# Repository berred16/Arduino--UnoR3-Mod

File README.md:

# Arduino--UnoR3-Mod
Some modifications of Arduino UNO R3 schematics

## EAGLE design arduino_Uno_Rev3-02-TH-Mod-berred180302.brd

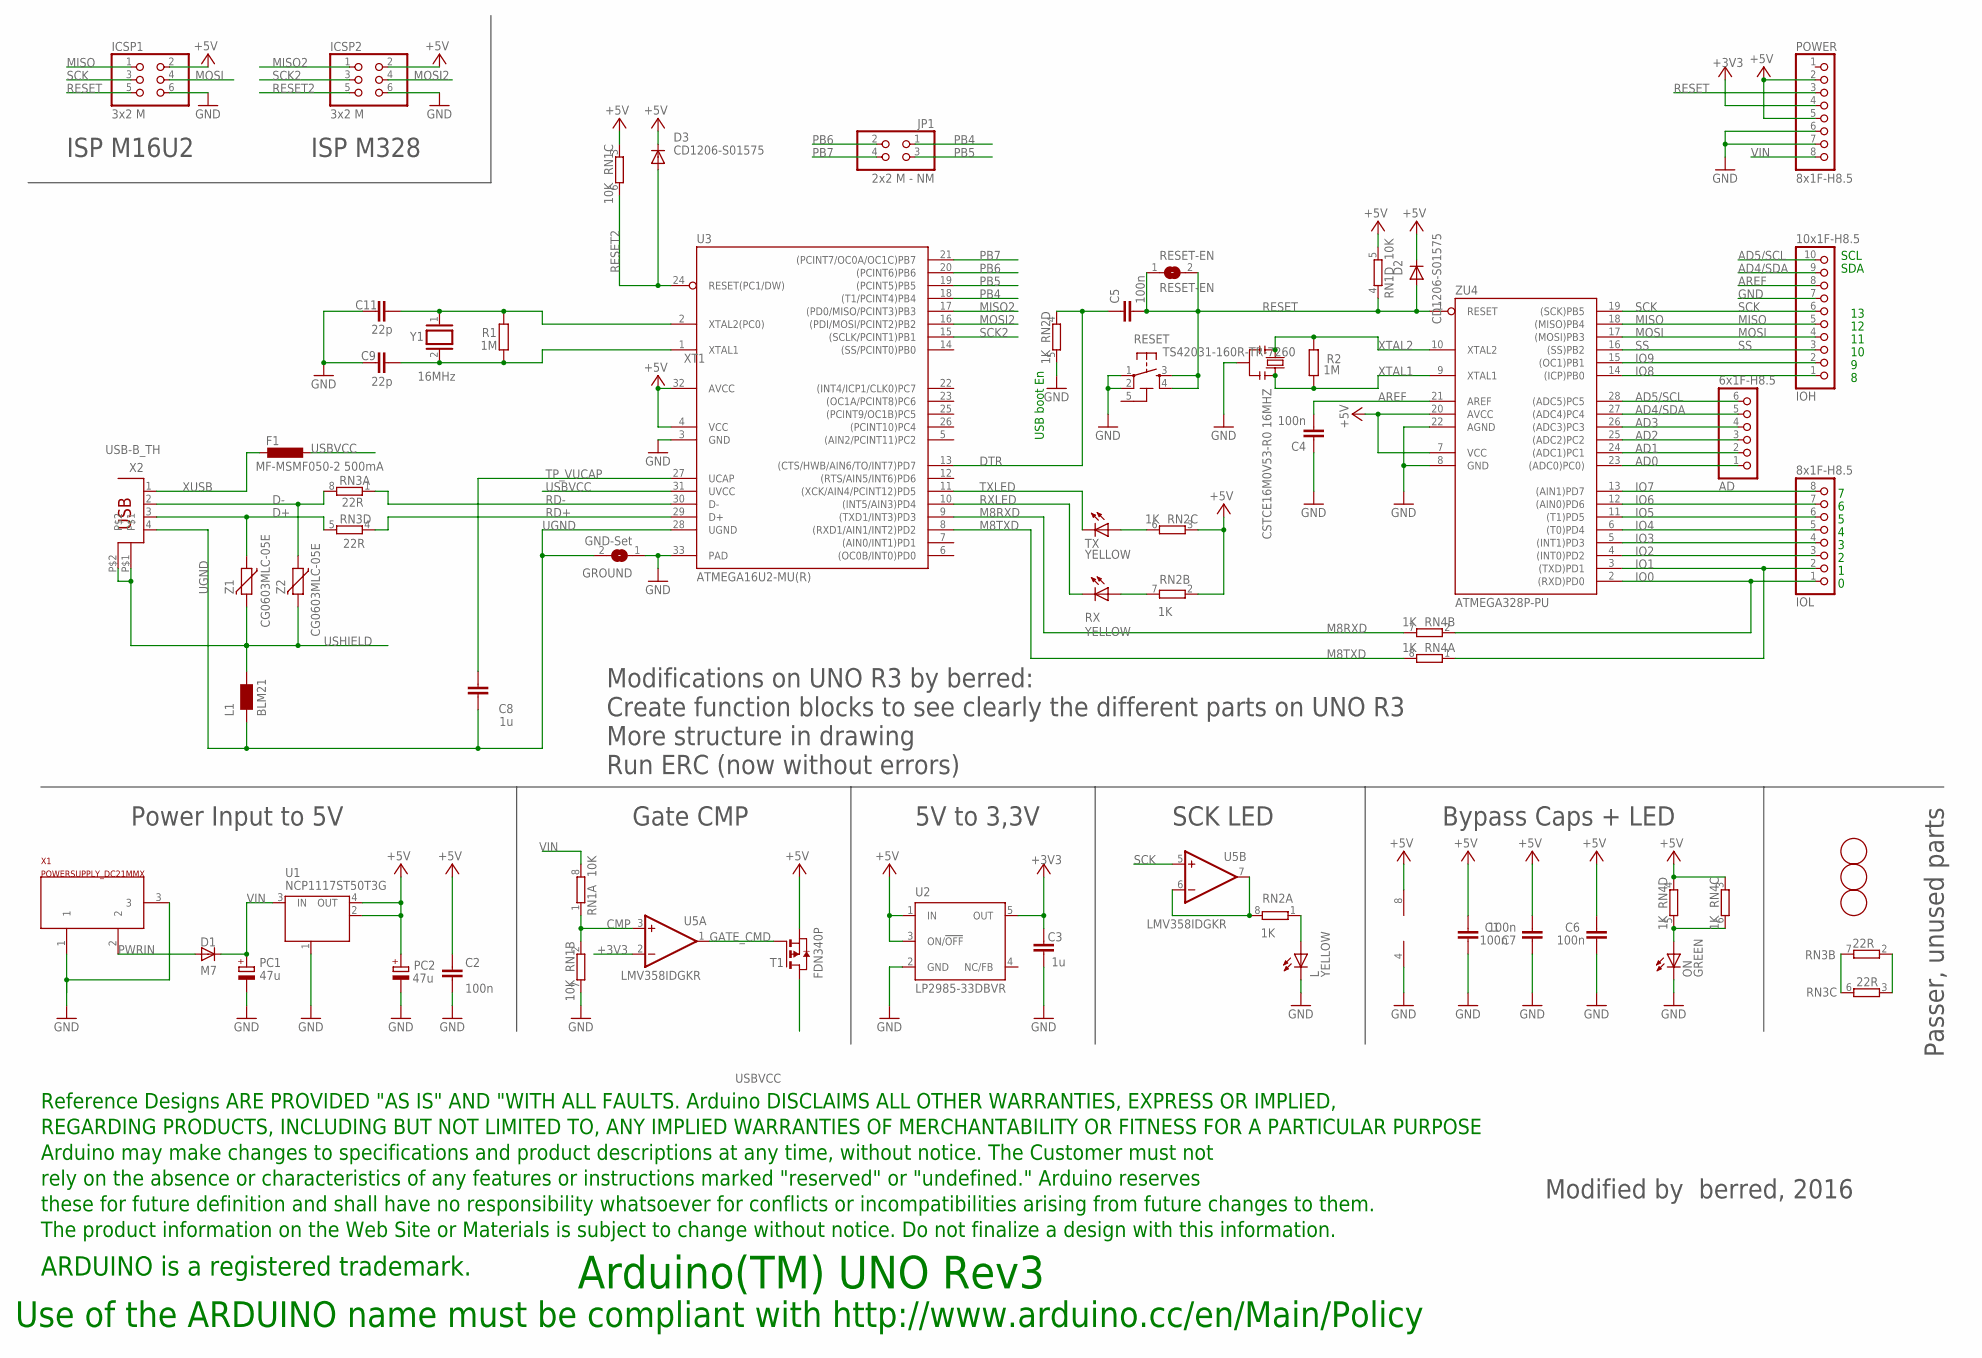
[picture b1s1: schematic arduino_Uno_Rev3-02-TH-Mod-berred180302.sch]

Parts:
AD: 6x1F-H8.5; 1X06
C1, C2, C4, C5, C6, C7: 100n; C0603-ROUND
C3, C8: 1u; C0603-ROUND
C9, C11: 22p; C0603-ROUND
D1: M7; SMB
D2, D3: CD1206-S01575; MINIMELF
F1: MF-MSMF050-2 500mA; L1812
FD1, FD2, FD3: FIDUCIALMOUNT; FIDUCIA-MOUNT
GROUND: GND-Set; SJ
ICSP1, ICSP2: 3x2 M; 2X03
IOH: 10x1F-H8.5; 1X10
IOL: 8x1F-H8.5; 1X08
JP1: 2x2 M - NM; 2X02
L: YELLOW; CHIP-LED0805
L1: BLM21; 0805
ON: GREEN; CHIP-LED0805
PC1, PC2: 47u; PANASONIC_D
POWER: 8x1F-H8.5; 1X08
R1, R2: 1M; R0603-ROUND
RESET: TS42031-160R-TR-7260; TS42
RESET-EN: RESET-EN; SJ
RN1: 10K; CAY16
RN2, RN4: 1K; CAY16
RN3: 22R; CAY16
RX: YELLOW; CHIP-LED0805
T1: FDN340P; SOT-23
TX: YELLOW; CHIP-LED0805
U1: NCP1117ST50T3G; SOT223
U2: LP2985-33DBVR; SOT23-DBV
U3: ATMEGA16U2-MU(R); MLF32
U5: LMV358IDGKR; MSOP08
U$1: DISCLAIMER
X1: POWERSUPPLY_DC21MMX; POWERSUPPLY_DC-21MM
X2: USB-B_TH; PN61729
Y1: 16MHz; QS
Y2: CSTCE16M0V53-R0 16MHZ; RESONATOR
Z1, Z2: CG0603MLC-05E; CT/CN0603
ZU4: ATMEGA328P-PU; DIL28-3

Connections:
5-GND: RESET.5 (5-GND)
+3V3: C3.2, POWER.4, U2.5 (OUT), U5.2 (-IN)
+5V: C1.2, C2.2, C6.2, C7.1, D2.C, D3.C, ICSP1.2, ICSP2.2, PC2.+, POWER.2, POWER.5, RN1.3 (1), RN1.5 (2), RN2.2 (1), RN2.3 (1), RN4.3 (1), RN4.4 (1), T1.2 (S), U1.2 (OUT), U1.4 (OUT), U2.1 (IN), U2.3 (ON/!OFF), U3.4 (VCC), U3.32 (AVCC), U5.8 (V+), ZU4.7 (VCC), ZU4.20 (AVCC)
AD0: AD.1, ZU4.23 ((ADC0)PC0))
AD1: AD.2, ZU4.24 ((ADC1)PC1)
AD2: AD.3, ZU4.25 ((ADC2)PC2)
AD3: AD.4, ZU4.26 ((ADC3)PC3)
AD4/SDA: AD.5, IOH.9, ZU4.27 ((ADC4)PC4)
AD5/SCL: AD.6, IOH.10, ZU4.28 ((ADC5)PC5)
AREF: C4.2, IOH.8, ZU4.21 (AREF)
CMP: RN1.1, RN1.2 (1), U5.3 (+IN)
D+: RN3.5 (2), X2.3, Z1.1
D-: RN3.8 (2), X2.2, Z2.1
DTR: C5.1, RN2.4 (1), U3.13 ((CTS/HWB/AIN6/TO/INT7)PD7)
GATE_CMD: T1.3 (G), U5.1 (OUT)
GND: C1.1, C2.1, C3.1, C4.1, C6.1, C7.2, C9.2, C11.2, GROUND.1, ICSP1.6, ICSP2.6, IOH.7, L.C, ON.C, PC1.-, PC2.-, POWER.6, POWER.7, RESET.1, RESET.2, RN1.7 (2), RN2.5 (2), U1.1 (GND/ADJ), U2.2 (GND), U3.3 (GND), U3.33 (PAD), U5.4 (V-), X1.1, X1.3, Y2.2, ZU4.8 (GND), ZU4.22 (AGND)
IO0: IOL.1, RN4.2 (1), ZU4.2 ((RXD)PD0)
IO1: IOL.2, RN4.1, ZU4.3 ((TXD)PD1)
IO2: IOL.3, ZU4.4 ((INT0)PD2)
IO3: IOL.4, ZU4.5 ((INT1)PD3)
IO4: IOL.5, ZU4.6 ((T0)PD4)
IO5: IOL.6, ZU4.11 ((T1)PD5)
IO6: IOL.7, ZU4.12 ((AIN0)PD6)
IO7: IOL.8, ZU4.13 ((AIN1)PD7)
IO8: IOH.1, ZU4.14 ((ICP)PB0)
IO9: IOH.2, ZU4.15 ((OC1)PB1)
L13: RN2.8 (2), U5.6 (-IN), U5.7 (OUT)
M8RXD: RN4.7 (2), U3.9 ((TXD1/INT3)PD3)
M8TXD: RN4.8 (2), U3.8 ((RXD1/AIN1/INT2)PD2)
MISO: ICSP1.1, IOH.5, ZU4.18 ((MISO)PB4)
MISO2: ICSP2.1, U3.17 ((PD0/MISO/PCINT3)PB3)
MOSI: ICSP1.4, IOH.4, ZU4.17 ((MOSI)PB3)
MOSI2: ICSP2.4, U3.16 ((PDI/MOSI/PCINT2)PB2)
unnamed: L.A, RN2.1
unnamed: RN3.2 (1), RN3.3 (1)
unnamed: ON.A, RN4.5 (2), RN4.6 (2)
unnamed: RN3.6 (2), RN3.7 (2)
unnamed: RN2.7 (2), RX.A
unnamed: RN2.6 (2), TX.A
PB4: JP1.1, U3.18 ((T1/PCINT4)PB4)
PB5: JP1.3, U3.19 ((PCINT5)PB5)
PB6: JP1.2, U3.20 ((PCINT6)PB6)
PB7: JP1.4, U3.21 ((PCINT7/OC0A/OC1C)PB7)
PWRIN: D1.A, X1.2
RD+: RN3.4 (1), U3.29 (D+)
RD-: RN3.1, U3.30 (D-)
RESET: C5.2, D2.A, ICSP1.5, POWER.3, RESET.3, RESET.4, RESET-EN.1, RESET-EN.2, RN1.4 (1), ZU4.1 (RESET)
RESET2: D3.A, ICSP2.5, RN1.6 (2), U3.24 (RESET(PC1/DW))
RXLED: RX.C, U3.10 ((INT5/AIN3)PD4)
SCK: ICSP1.3, IOH.6, U5.5 (+IN), ZU4.19 ((SCK)PB5)
SCK2: ICSP2.3, U3.15 ((SCLK/PCINT1)PB1)
SS: IOH.3, ZU4.16 ((SS)PB2)
TP_VUCAP: C8.1, U3.27 (UCAP)
TXLED: TX.C, U3.11 ((XCK/AIN4/PCINT12)PD5)
UGND: C8.2, GROUND.2, L1.1, U3.28 (UGND), X2.4
USBVCC: F1.1, T1.1 (D), U3.31 (UVCC)
USHIELD: L1.2, X2.P$1, X2.P$2, Z1.2, Z2.2
VIN: D1.C, PC1.+, POWER.8, RN1.8 (2), U1.3 (IN)
XT1: C9.1, R1.1, U3.1 (XTAL1), Y1.2
XT2: C11.1, R1.2, U3.2 (XTAL2(PC0)), Y1.1
XTAL1: R2.1, Y2.3, ZU4.9 (XTAL1)
XTAL2: R2.2, Y2.1, ZU4.10 (XTAL2)
XUSB: F1.2, X2.1

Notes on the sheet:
Arduino(TM) UNO Rev3
USB boot En
SDA
SCL
Use of the ARDUINO name must be compliant with http://www.arduino.cc/en/Main/Policy
Modified by berred, 2016
Power Input to 5V
Gate CMP
5V to 3,3V
SCK LED
Bypass Caps + LED
Passer, unused parts
ISP M16U2
ISP M328
Modifications on UNO R3 by berred: Create function blocks to see clearly the different parts on UNO R3 More structure in drawing Run ERC (now without errors)

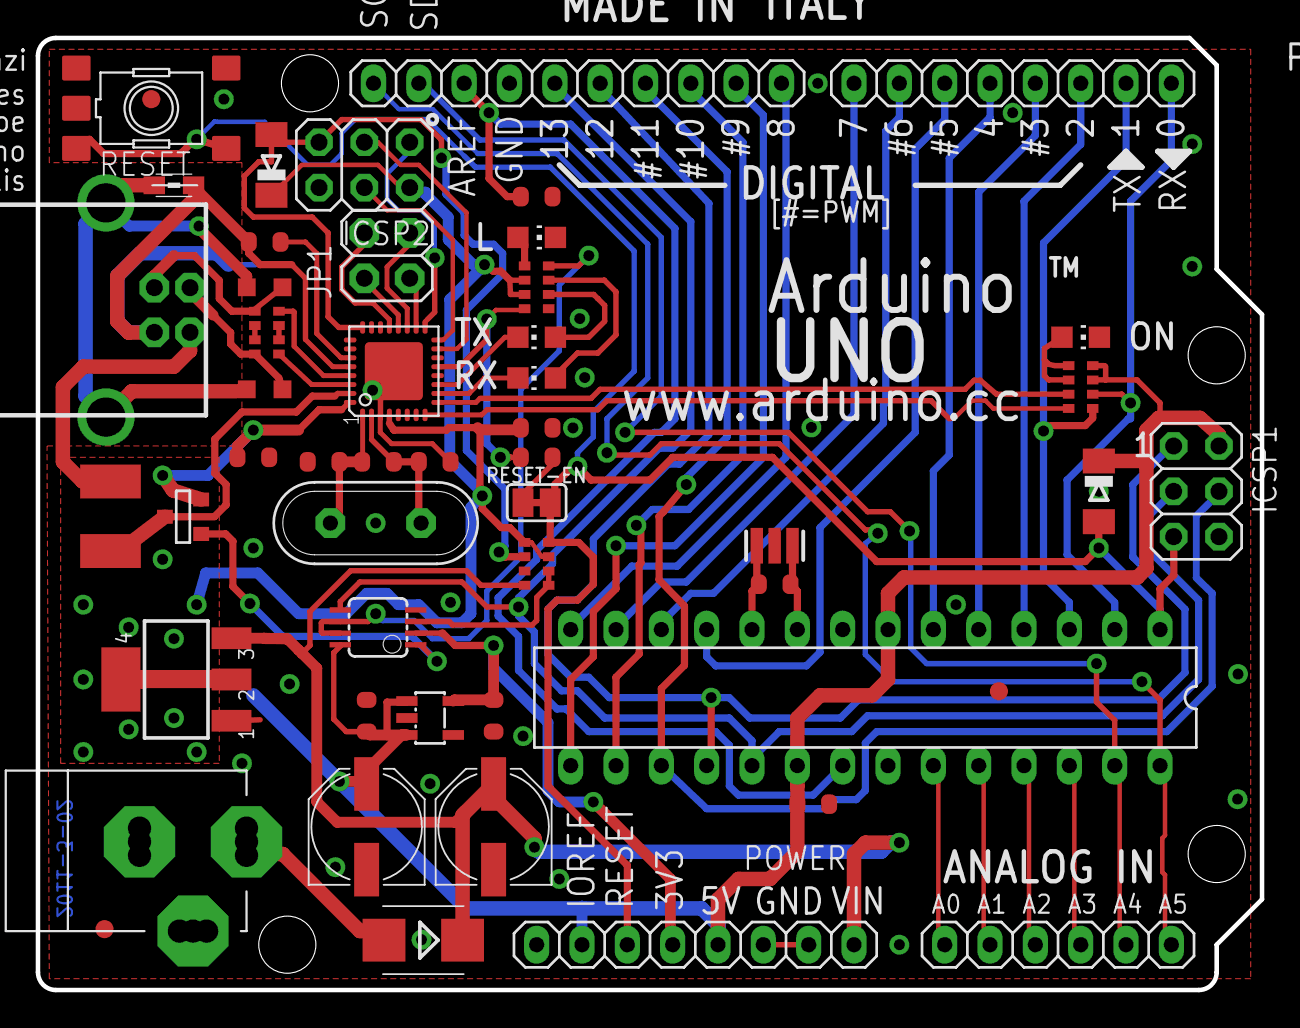
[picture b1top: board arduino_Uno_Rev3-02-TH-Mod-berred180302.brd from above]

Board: 2 copper layers, 68.6 x 53.3 mm, 53 parts (1 on the bottom side), 62 nets.
